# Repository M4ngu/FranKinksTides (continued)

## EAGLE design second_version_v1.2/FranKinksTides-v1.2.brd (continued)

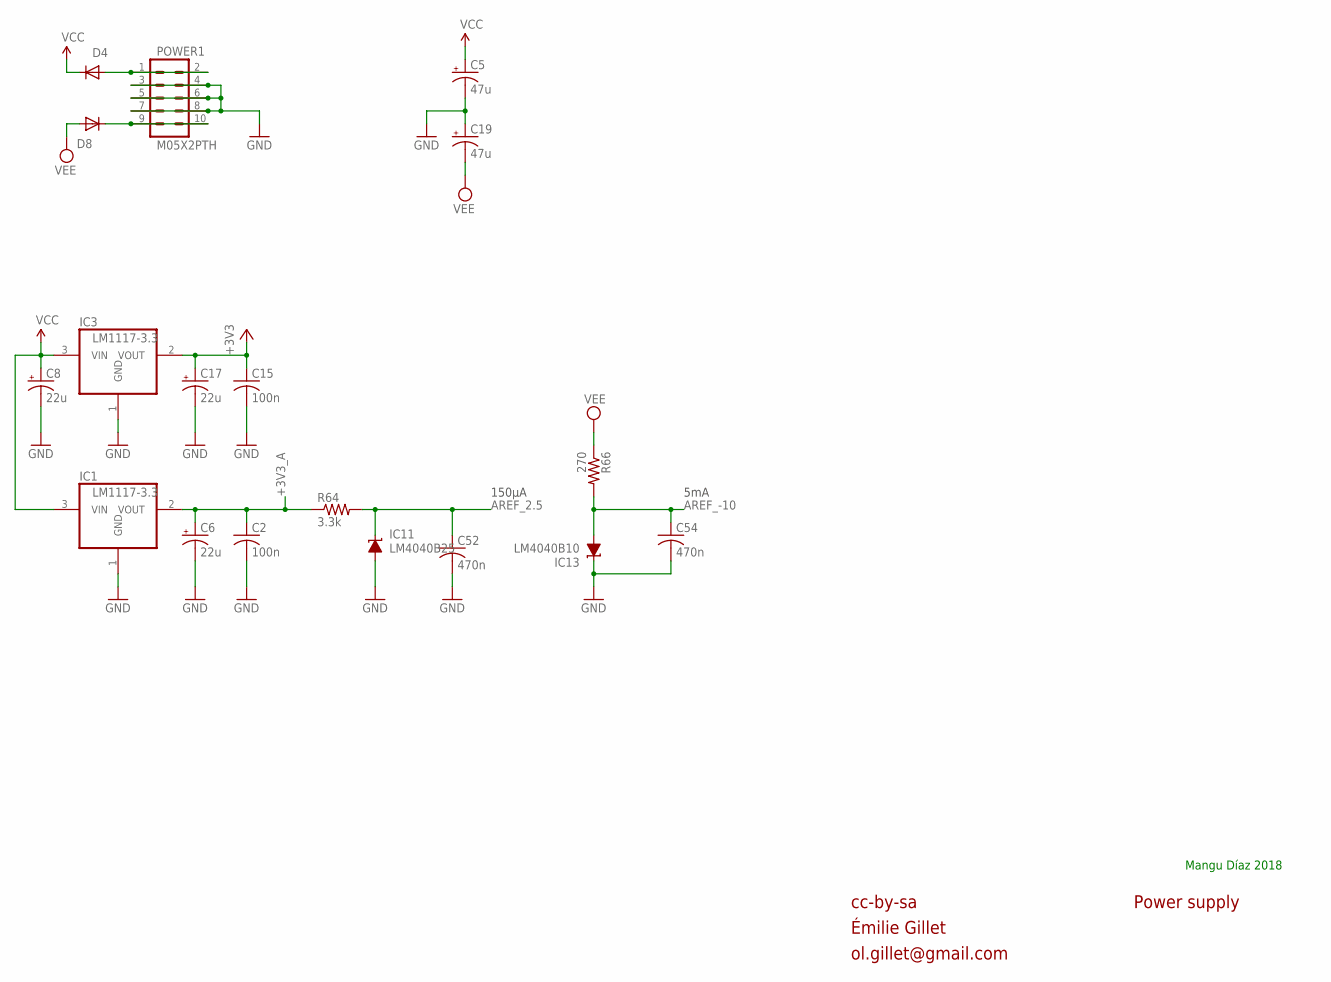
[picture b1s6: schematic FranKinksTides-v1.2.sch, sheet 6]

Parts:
C2, C15: 100n; C0603
C5, C19: 47u; PANASONIC_D
C6, C8, C17: 22u; PANASONIC_C
C52, C54: 470n; C0603
D4, D8: 1N5819HW; SOD123
IC1, IC3: LM1117-3.3; SOT223
IC11: LM4040B25; DBZ_R-PDSO-G3
IC13: LM4040B10; DBZ_R-PDSO-G3
POWER1: M05X2PTH; AVR_ICSP
R64: 3.3k; R0603
R66: 270; R0603

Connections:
+3V3: C15.1, C17.+, IC3.2 (VOUT); also elsewhere on the board
+3V3_A: C2.1, C6.+, IC1.2 (VOUT), R64.1; also elsewhere on the board
AREF_2.5: C52.1, IC11.1 (C), R64.2; also elsewhere on the board
AREF_-10: C54.1, IC13.2 (A), R66.2; also elsewhere on the board
GND: C2.2, C5.-, C6.-, C8.-, C15.2, C17.-, C19.+, C52.2, C54.2, IC1.1 (GND), IC3.1 (GND), IC11.2 (A), IC13.1 (C), POWER1.3, POWER1.4, POWER1.5, POWER1.6, POWER1.7, POWER1.8; also elsewhere on the board
unnamed: D4.A, POWER1.1, POWER1.2
unnamed: D8.C, POWER1.9, POWER1.10
VCC: C5.+, C8.+, D4.C, IC1.3 (VIN), IC3.3 (VIN); also elsewhere on the board
VEE: C19.-, D8.A, R66.1; also elsewhere on the board

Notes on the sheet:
cc-by-sa
Émilie Gillet
ol.gillet@gmail.com
Power supply
5mA
150µA
Mangu Díaz 2018

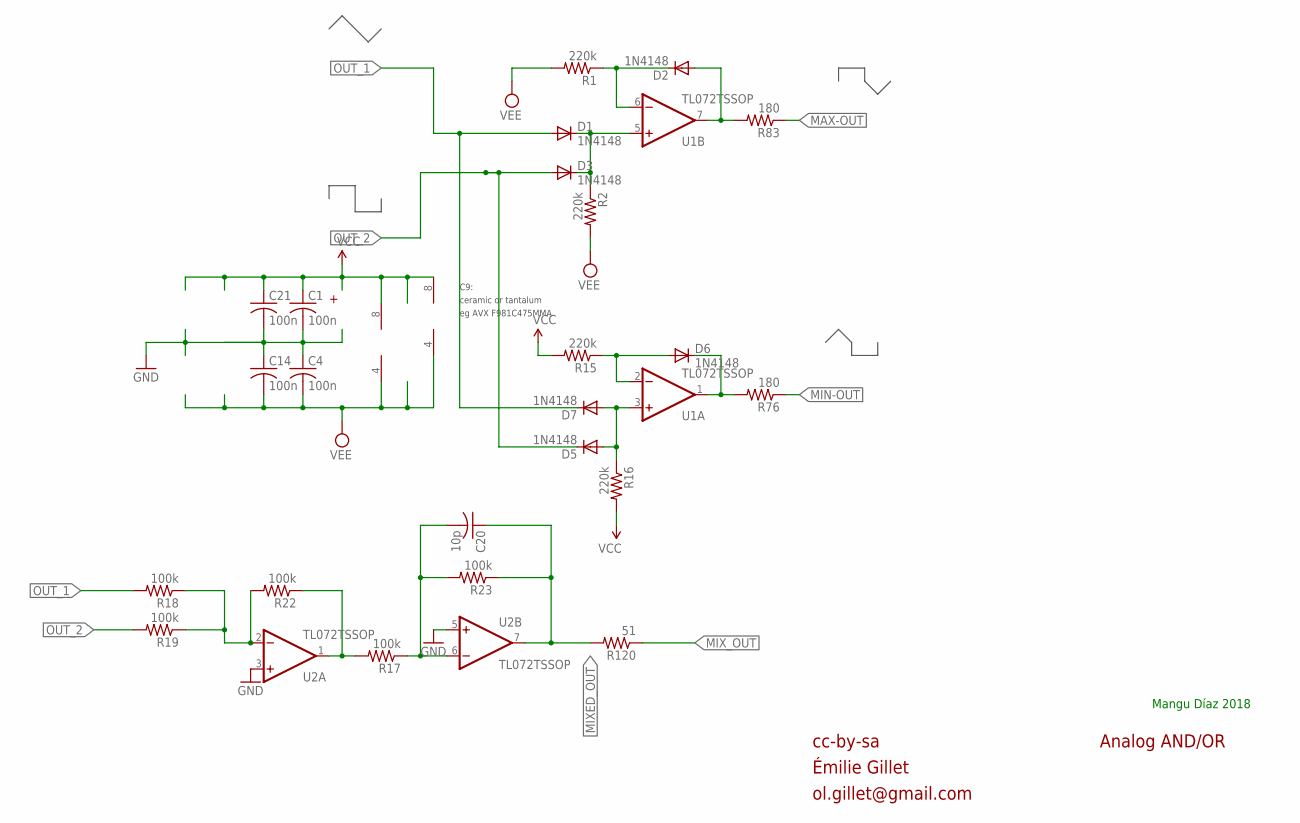
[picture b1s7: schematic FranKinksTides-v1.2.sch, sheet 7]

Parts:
C1, C4, C14, C21: 100n; C0603
C20: 10p; C0603
D1, D2, D3, D5, D6, D7: 1N4148; SOD123
R1, R2, R15, R16: 220k; R0603
R17, R18, R19, R22, R23: 100k; R0603
R76, R83: 180; R0603
R120: 51; R0603
U1, U2: TL072TSSOP; TSSOP-8

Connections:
GND: C1.2, C4.1, C14.1, C21.2, U2.3 (+IN), U2.5 (+IN); also elsewhere on the board
MAX-OUT: R83.1; also elsewhere on the board
MIN-OUT: R76.1; also elsewhere on the board
MIXED_OUT: C20.1, R23.1, R120.2, U2.7 (OUT)
MIX_OUT: R120.1; also elsewhere on the board
unnamed: R17.2, R22.1, U2.1 (OUT)
unnamed: D1.C, D3.C, R2.1, U1.5 (+IN)
unnamed: D2.A, R83.2, U1.7 (OUT)
unnamed: C20.2, R17.1, R23.2, U2.6 (-IN)
unnamed: R18.1, R19.1, R22.2, U2.2 (-IN)
unnamed: D2.C, R1.1, U1.6 (-IN)
unnamed: D5.A, D7.A, R16.1, U1.3 (+IN)
unnamed: D6.C, R76.2, U1.1 (OUT)
unnamed: D6.A, R15.1, U1.2 (-IN)
OUT_1: D1.A, D7.C, R18.2; also elsewhere on the board
OUT_2: D3.A, D5.C, R19.2; also elsewhere on the board
VCC: C1.1, C21.1, R15.2, R16.2, U1.8 (V+), U2.8 (V+); also elsewhere on the board
VEE: C4.2, C14.2, R1.2, R2.2, U1.4 (V-), U2.4 (V-); also elsewhere on the board

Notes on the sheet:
cc-by-sa
Émilie Gillet
ol.gillet@gmail.com
Analog AND/OR
eg AVX F981C475MMA
ceramic or tantalum
C9:
Mangu Díaz 2018

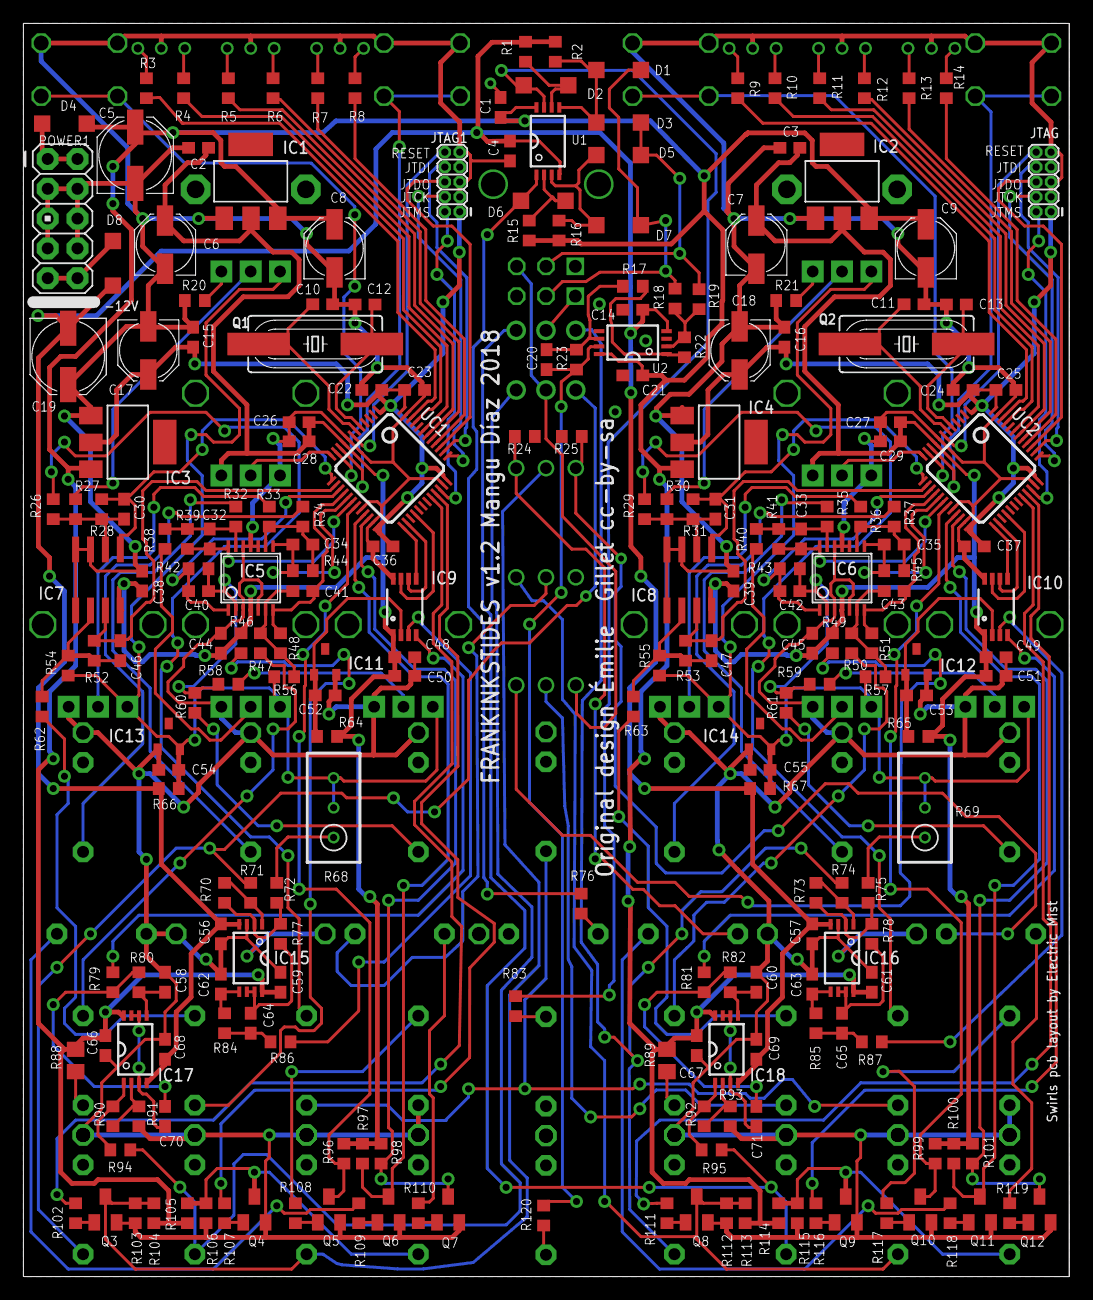
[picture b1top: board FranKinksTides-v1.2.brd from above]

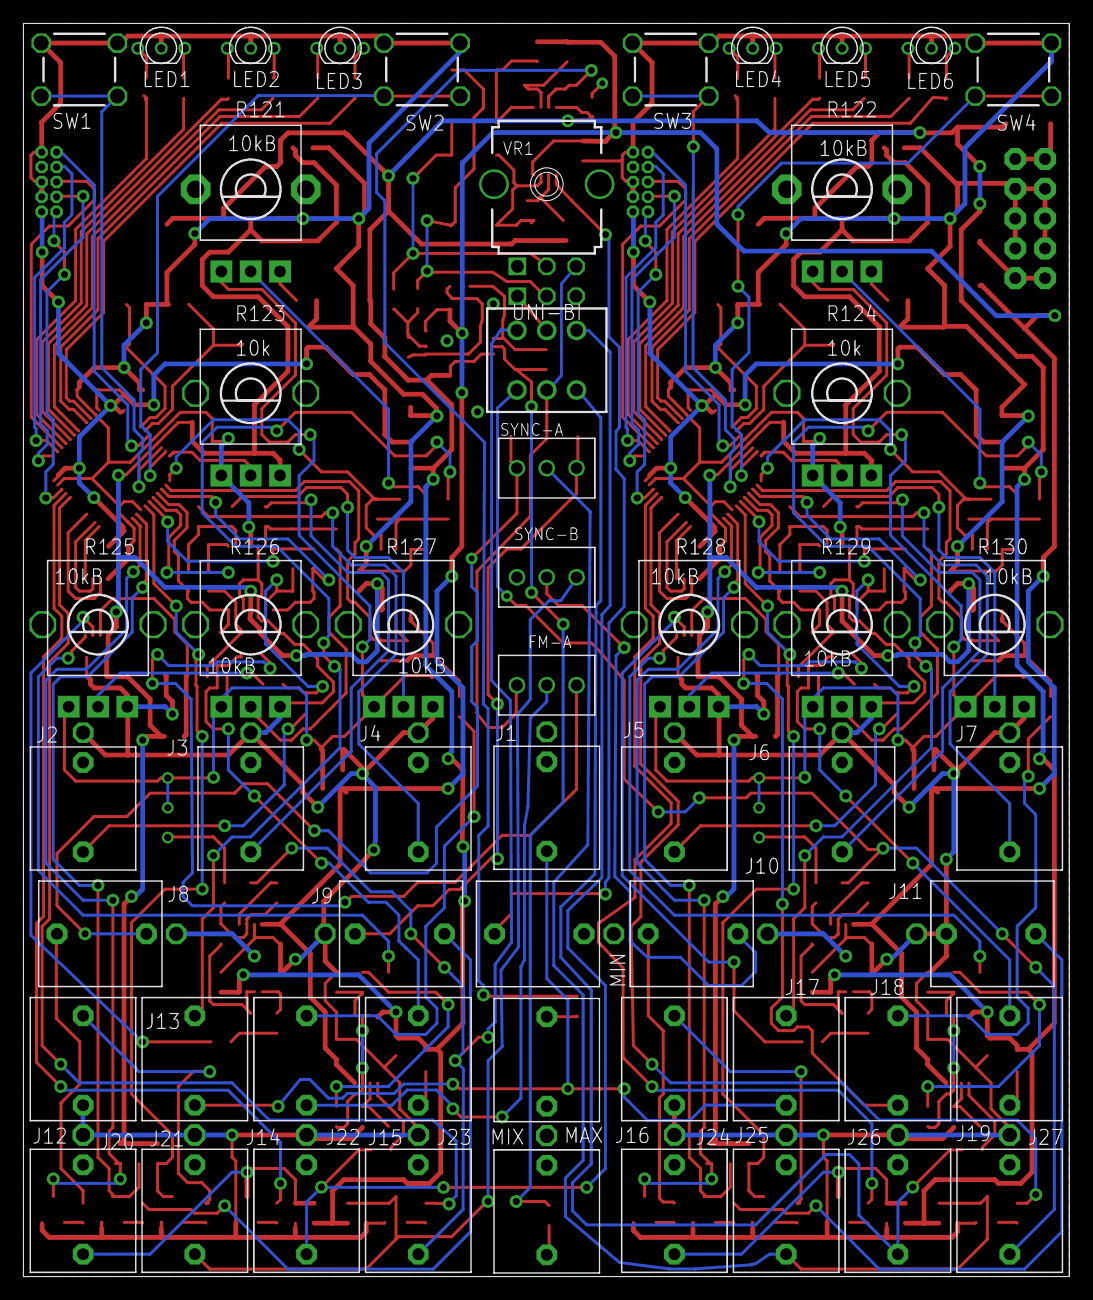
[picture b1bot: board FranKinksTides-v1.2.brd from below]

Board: 2 copper layers, 89.1 x 106.8 mm, 291 parts (55 on the bottom side), 170 nets.

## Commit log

2020-06-14 first version added
2020-06-14 files uploaded
2020-06-14 second and last version added
